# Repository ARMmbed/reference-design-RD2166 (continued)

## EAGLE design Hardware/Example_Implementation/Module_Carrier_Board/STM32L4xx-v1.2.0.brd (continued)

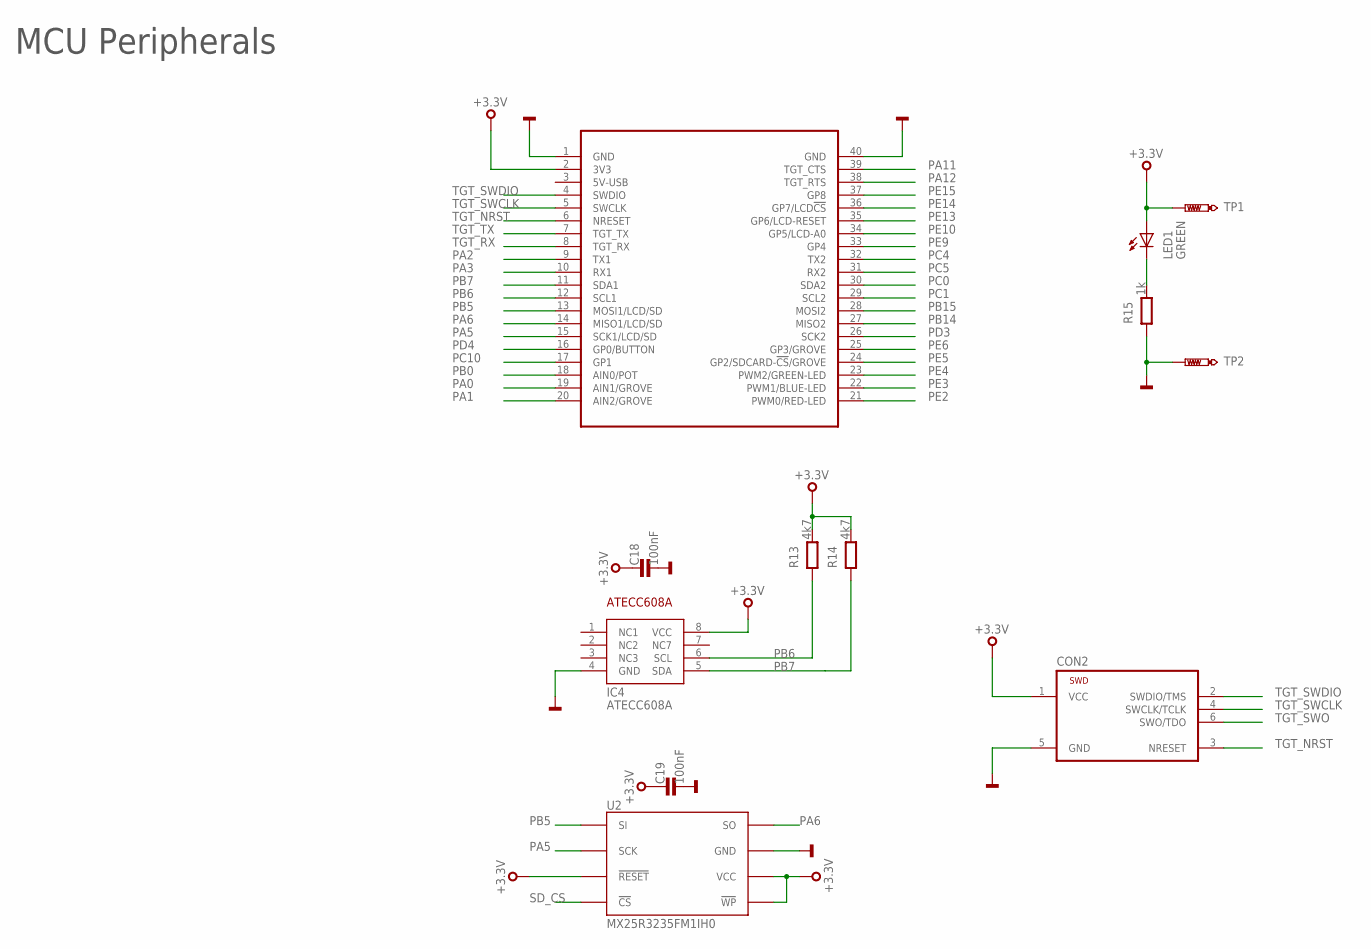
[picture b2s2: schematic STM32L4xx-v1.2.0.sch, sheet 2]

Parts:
C18, C19: 100nF; 0402
CON2: TC2030-CTX-NL
IC4: ATECC608A; SO8
LED1: GREEN; CHIPLED_0603
MOD1: MODULE_DAUGHTER
R13, R14: 4k7; 0402
R15: 1k; 0603
TP1, TP2: TEST_POINT-50R-PTH; TP50-PTH
U2: MX25R3235FM1IH0; SO8

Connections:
+3.3V: C18.1, C19.1, CON2.1 (VCC), IC4.8 (VCC), LED1.A, MOD1.2 (3V3), R13.2, R14.2, TP1.TP, U2.3 (!WP), U2.7 (!RESET), U2.8 (VCC); also elsewhere on the board
GND: C18.2, C19.2, CON2.5 (GND), IC4.4 (GND), MOD1.1 (GND), MOD1.40 (GND), R15.1, TP2.TP, U2.4 (GND); also elsewhere on the board
PA0: MOD1.19 (AIN1/GROVE); also elsewhere on the board
PA1: MOD1.20 (AIN2/GROVE); also elsewhere on the board
PA2: MOD1.9 (TX1); also elsewhere on the board
PA3: MOD1.10 (RX1); also elsewhere on the board
PA5: MOD1.15 (SCK1/LCD/SD), U2.6 (SCK); also elsewhere on the board
PA6: MOD1.14 (MISO1/LCD/SD), U2.2 (SO); also elsewhere on the board
PA11: MOD1.39 (TGT_CTS); also elsewhere on the board
PA12: MOD1.38 (TGT_RTS); also elsewhere on the board
PA_1: LED1.C, R15.2
PB0: MOD1.18 (AIN0/POT); also elsewhere on the board
PB5: MOD1.13 (MOSI1/LCD/SD), U2.5 (SI); also elsewhere on the board
PB6: IC4.6 (SCL), MOD1.12 (SCL1), R13.1; also elsewhere on the board
PB7: IC4.5 (SDA), MOD1.11 (SDA1), R14.1; also elsewhere on the board
PB14: MOD1.27 (MISO2); also elsewhere on the board
PB15: MOD1.28 (MOSI2); also elsewhere on the board
PC0: MOD1.30 (SDA2); also elsewhere on the board
PC1: MOD1.29 (SCL2); also elsewhere on the board
PC4: MOD1.32 (TX2); also elsewhere on the board
PC5: MOD1.31 (RX2); also elsewhere on the board
PC10: MOD1.17 (GP1); also elsewhere on the board
PD3: MOD1.26 (SCK2); also elsewhere on the board
PD4: MOD1.16 (GP0/BUTTON); also elsewhere on the board
PE2: MOD1.21 (PWM0/RED-LED); also elsewhere on the board
PE3: MOD1.22 (PWM1/BLUE-LED); also elsewhere on the board
PE4: MOD1.23 (PWM2/GREEN-LED); also elsewhere on the board
PE5: MOD1.24 (GP2/SDCARD-!CS!/GROVE); also elsewhere on the board
PE6: MOD1.25 (GP3/GROVE); also elsewhere on the board
PE9: MOD1.33 (GP4); also elsewhere on the board
PE10: MOD1.34 (GP5/LCD-A0); also elsewhere on the board
PE13: MOD1.35 (GP6/LCD-RESET); also elsewhere on the board
PE14: MOD1.36 (GP7/LCD!CS); also elsewhere on the board
PE15: MOD1.37 (GP8); also elsewhere on the board
SD_CS: U2.1 (!CS); also elsewhere on the board
TGT_NRST: CON2.3 (NRESET), MOD1.6 (NRESET); also elsewhere on the board
TGT_RX: MOD1.8 (TGT_RX); also elsewhere on the board
TGT_SWCLK: CON2.4 (SWCLK/TCLK), MOD1.5 (SWCLK); also elsewhere on the board
TGT_SWDIO: CON2.2 (SWDIO/TMS), MOD1.4 (SWDIO); also elsewhere on the board
TGT_SWO: CON2.6 (SWO/TDO); also elsewhere on the board
TGT_TX: MOD1.7 (TGT_TX); also elsewhere on the board

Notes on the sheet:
MCU Peripherals

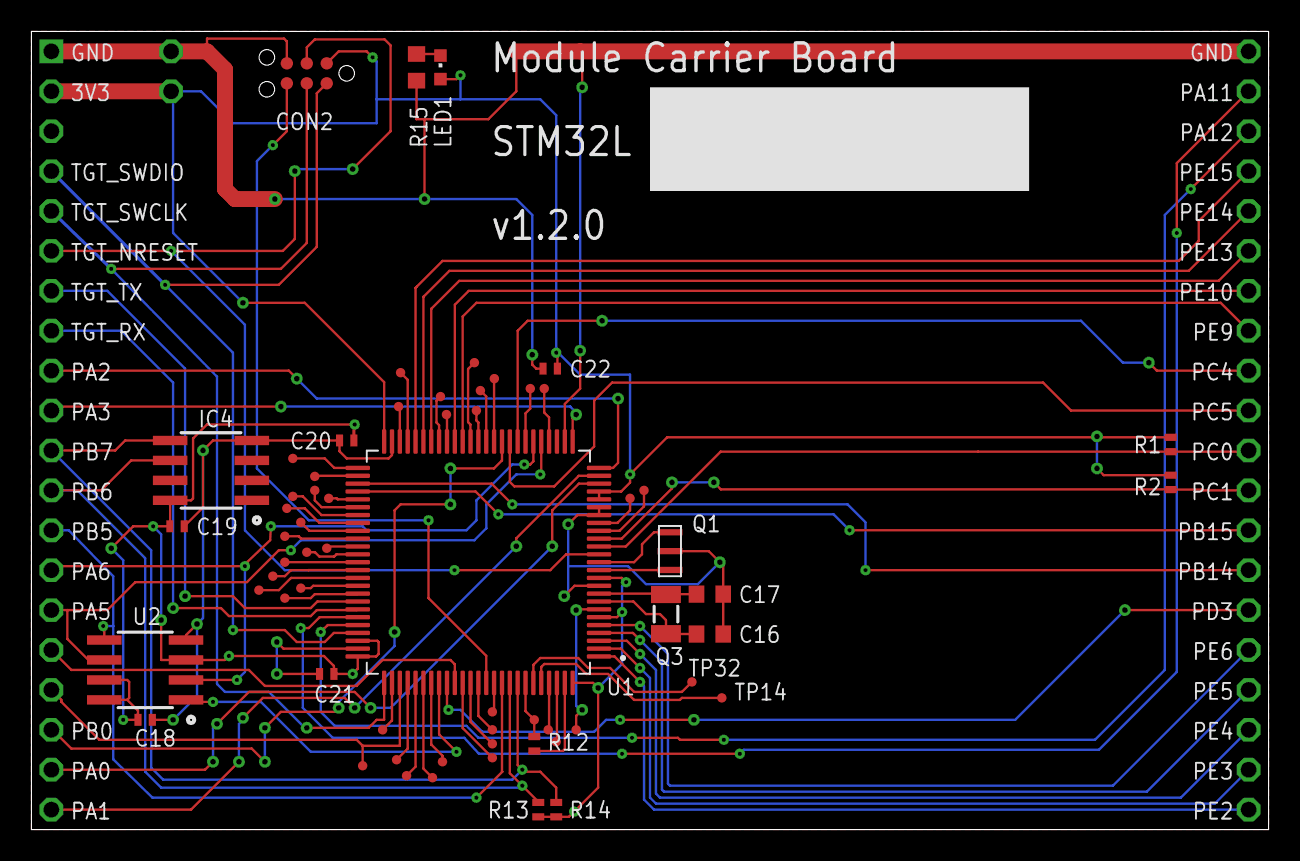
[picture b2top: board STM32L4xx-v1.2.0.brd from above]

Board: 2 copper layers, 78.7 x 50.8 mm, 66 parts (0 on the bottom side), 87 nets.

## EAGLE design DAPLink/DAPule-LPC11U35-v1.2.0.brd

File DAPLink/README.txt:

/*********************************
        DAPule
*********************************/

There are many flavours of DAPule available with different MCU's such as an LPC11U35, K20D, KL26Z and others.

For the purposes of this reference design, we have used an LPC11U35 based DAPule, schematics and design files 
for which have been shared in this directory.

Also, a binary file that was used for development of this RD2166 on the MTB (schematics and design files also
shared) is available for use.

For any issues, please use the RD2166's GitHub repo to report issues.

       ********** End of document *********

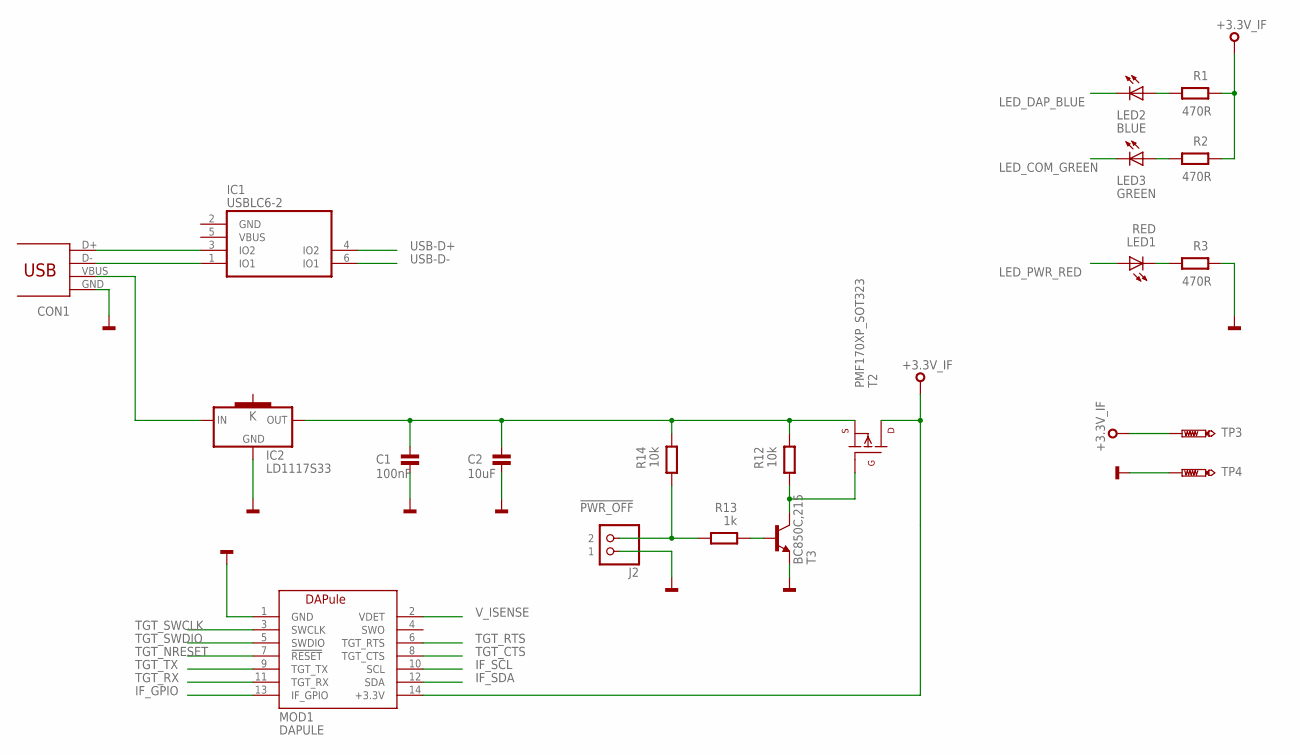
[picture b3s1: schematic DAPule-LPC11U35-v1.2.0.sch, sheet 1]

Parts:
C1: 100nF; 0603
C2: 10uF; 0603
CON1: USB_MICROB; MOLEX-47364-0001
IC1: USBLC6-2SC6; SOT23-6L
IC2: LD1117S33; SOT223
J2: PINHD-1X2; 1X02
LED1: RED; CHIPLED_0603
LED2: BLUE; CHIPLED_0603
LED3: GREEN; CHIPLED_0603
MOD1: DAPULE
R1, R2, R3: 470R; 0603@1
R12, R14: 10k; 0603@1
R13: 1k; 0603@1
T2: PMF170XP_SOT323; SOT323-BEC
T3: BC850C,215; SOT23-3
TP3, TP4: TEST-POINT-50R-PTH; TP50-PTH

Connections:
!PWR_OFF: J2.2, R13.2, R14.2
+3.3V_IF: MOD1.14 (+3.3V), R1.1, R2.1, T2.C (D), TP3.TP; also elsewhere on the board
GND: C1.2, C2.2, CON1.GND, IC2.1 (GND), J2.1, MOD1.1 (GND), R3.1, T3.2 (E), TP4.TP; also elsewhere on the board
IF_GPIO: MOD1.13 (IF_GPIO); also elsewhere on the board
IF_SCL: MOD1.10 (SCL); also elsewhere on the board
IF_SDA: MOD1.12 (SDA); also elsewhere on the board
LED_COM_GREEN: LED3.C; also elsewhere on the board
LED_DAP_BLUE: LED2.C; also elsewhere on the board
LED_PWR_RED: LED1.A; also elsewhere on the board
unnamed: LED3.A, R2.2
unnamed: CON1.D-, IC1.1 (IO1)
unnamed: CON1.D+, IC1.3 (IO2)
unnamed: LED2.A, R1.2
unnamed: C1.1, C2.1, IC2.2 (OUT), R12.1, R14.1, T2.E (S)
unnamed: LED1.C, R3.2
unnamed: CON1.VBUS, IC2.3 (IN)
unnamed: R13.1, T3.1 (B)
unnamed: R12.2, T2.B (G), T3.3 (C)
TGT_CTS: MOD1.8 (TGT_CTS); also elsewhere on the board
TGT_NRESET: MOD1.7 (!RESET); also elsewhere on the board
TGT_RTS: MOD1.6 (TGT_RTS); also elsewhere on the board
TGT_RX: MOD1.11 (TGT_RX); also elsewhere on the board
TGT_SWCLK: MOD1.3 (SWCLK); also elsewhere on the board
TGT_SWDIO: MOD1.5 (SWDIO); also elsewhere on the board
TGT_TX: MOD1.9 (TGT_TX); also elsewhere on the board
USB-D+: IC1.4 (IO2); also elsewhere on the board
USB-D-: IC1.6 (IO1); also elsewhere on the board
V_ISENSE: MOD1.2 (VDET); also elsewhere on the board

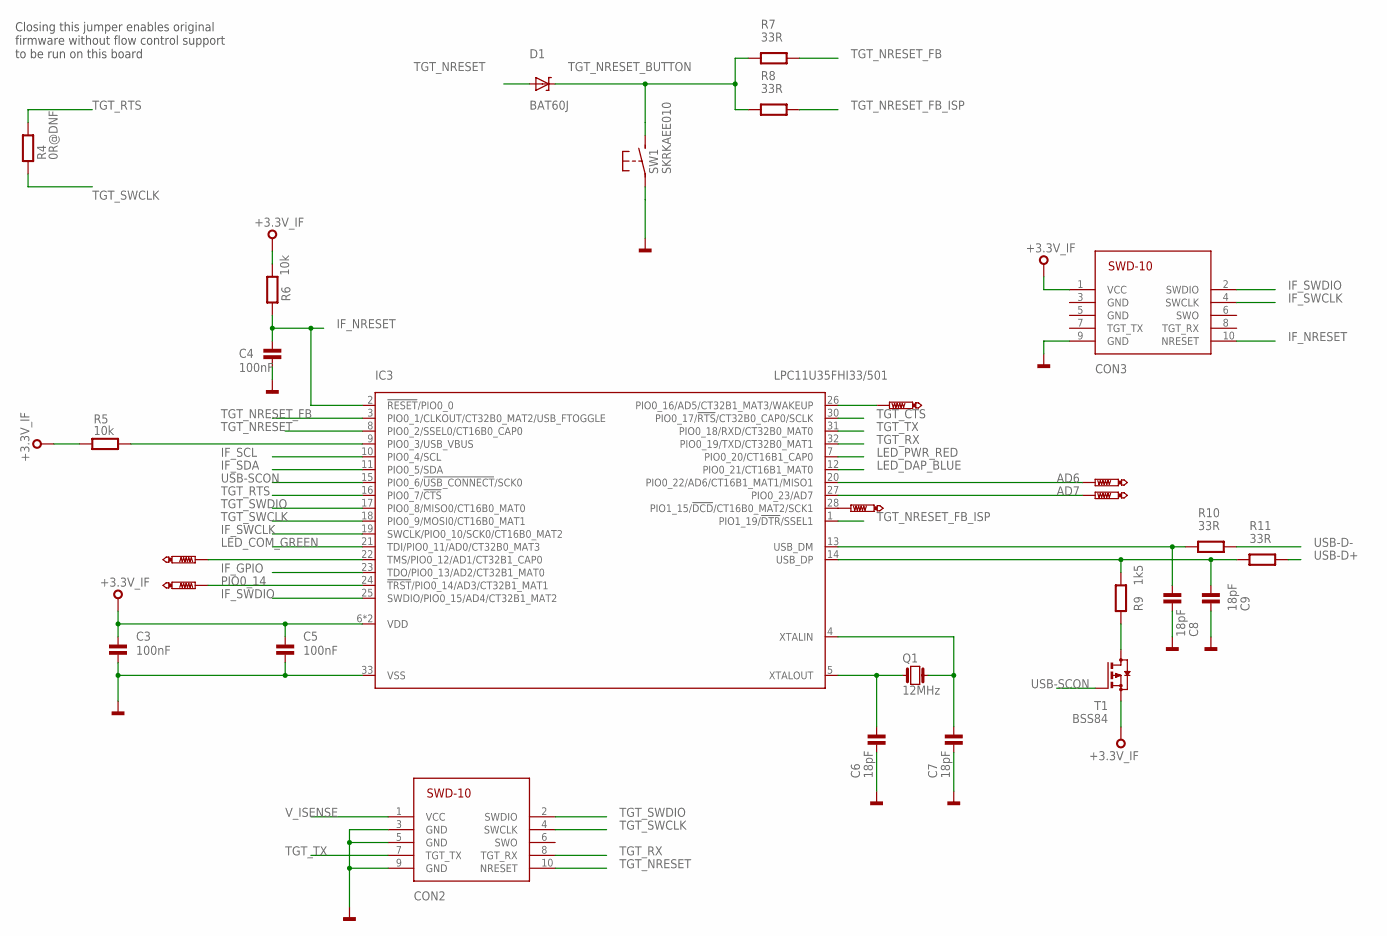
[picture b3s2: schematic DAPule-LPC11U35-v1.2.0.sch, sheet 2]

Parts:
C3, C4, C5: 100nF; 0603
C6, C7, C8, C9: 18pF; 0603
CON2, CON3: SWD-10/TC2050_SMD; FTSH-105-02
D1: BAT60J; SOD323
IC3: LPC11U35FHI33/501; SOT617-3
Q1: 12MHz; 3.2X.2.5
R4: 0R@DNF; 0402@1
R5, R6: 10k; 0603@1
R7, R8, R10, R11: 33R; 0603@1
R9: 1k5; 0603@1
SW1: SKRKAEE010
T1: BSS84; SOT23
TP1, TP2, TP5, TP8, TP9, TP13: PTR1TP07R; TP07R

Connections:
+3.3V_IF: C3.1, C5.1, CON3.1 (VCC), IC3.6 (VDD), IC3.29 (VDD), R5.2, R6.2, T1.2 (S); also elsewhere on the board
AD6: IC3.20 (PIO0_22/AD6/CT16B1_MAT1/MISO1), TP9.TP
AD7: IC3.27 (PIO0_23/AD7), TP8.TP
GND: C3.2, C4.2, C5.2, C6.2, C7.2, C8.2, C9.2, CON2.3 (GND), CON2.5 (GND), CON2.9 (GND), CON3.9 (GND), IC3.33 (VSS), SW1.P$1; also elsewhere on the board
IF_GPIO: IC3.23 (TDO/PIO0_13/AD2/CT32B1_MAT0); also elsewhere on the board
IF_NRESET: C4.1, CON3.10 (NRESET), IC3.2 (!RESET!/PIO0_0), R6.1
IF_SCL: IC3.10 (PIO0_4/SCL); also elsewhere on the board
IF_SDA: IC3.11 (PIO0_5/SDA); also elsewhere on the board
IF_SWCLK: CON3.4 (SWCLK), IC3.19 (SWCLK/PIO0_10/SCK0/CT16B0_MAT2)
IF_SWDIO: CON3.2 (SWDIO), IC3.25 (SWDIO/PIO0_15/AD4/CT32B1_MAT2)
LED_COM_GREEN: IC3.21 (TDI/PIO0_11/AD0/CT32B0_MAT3); also elsewhere on the board
LED_DAP_BLUE: IC3.12 (PIO0_21/CT16B1_MAT0); also elsewhere on the board
LED_PWR_RED: IC3.7 (PIO0_20/CT16B1_CAP0); also elsewhere on the board
unnamed: IC3.22 (TMS/PIO0_12/AD1/CT32B1_CAP0), TP1.TP
unnamed: IC3.26 (PIO0_16/AD5/CT32B1_MAT3/WAKEUP), TP2.TP
unnamed: IC3.28 (PIO1_15/!DCD!/CT16B0_MAT2/SCK1), TP5.TP
unnamed: C6.1, IC3.5 (XTALOUT), Q1.P$1 (1)
unnamed: C7.1, IC3.4 (XTALIN), Q1.P$3 (2)
unnamed: IC3.9 (PIO0_3/USB_VBUS), R5.1
unnamed: R9.1, T1.3 (D)
PIO0_14: IC3.24 (!TRST!/PIO0_14/AD3/CT32B1_MAT1), TP13.TP
TGT_CTS: IC3.30 (PIO0_17/!RTS!/CT32B0_CAP0/SCLK); also elsewhere on the board
TGT_NRESET: CON2.10 (NRESET), D1.A, IC3.8 (PIO0_2/SSEL0/CT16B0_CAP0); also elsewhere on the board
TGT_NRESET_BUTTON: D1.K, R7.2, R8.2, SW1.P$2 (S)
TGT_NRESET_FB: IC3.3 (PIO0_1/CLKOUT/CT32B0_MAT2/USB_FTOGGLE), R7.1
TGT_NRESET_FB_ISP: IC3.1 (PIO1_19/!DTR!/SSEL1), R8.1
TGT_RTS: IC3.16 (PIO0_7/!CTS!), R4.2; also elsewhere on the board
TGT_RX: CON2.8 (TGT_RX), IC3.32 (PIO0_19/TXD/CT32B0_MAT1); also elsewhere on the board
TGT_SWCLK: CON2.4 (SWCLK), IC3.18 (PIO0_9/MOSI0/CT16B0_MAT1), R4.1; also elsewhere on the board
TGT_SWDIO: CON2.2 (SWDIO), IC3.17 (PIO0_8/MISO0/CT16B0_MAT0); also elsewhere on the board
TGT_TX: CON2.7 (TGT_TX), IC3.31 (PIO0_18/RXD/CT32B0_MAT0); also elsewhere on the board
USB-D+: R11.1; also elsewhere on the board
USB-D-: R10.1; also elsewhere on the board
USB-SCON: IC3.15 (PIO0_6/!USB_CONNECT!/SCK0), T1.1 (G)
USB_DM: C8.1, IC3.13 (USB_DM), R10.2
USB_DP: C9.1, IC3.14 (USB_DP), R9.2, R11.2
V_ISENSE: CON2.1 (VCC); also elsewhere on the board

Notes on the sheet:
Closing this jumper enables original firmware without flow control support to be run on this board

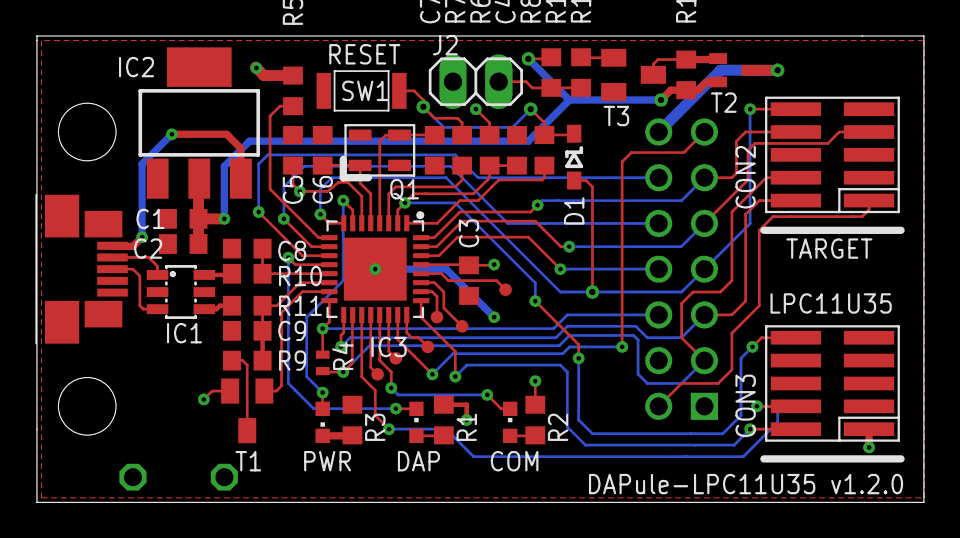
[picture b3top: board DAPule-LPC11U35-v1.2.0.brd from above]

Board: 2 copper layers, 49.3 x 25.9 mm, 48 parts (0 on the bottom side), 47 nets.

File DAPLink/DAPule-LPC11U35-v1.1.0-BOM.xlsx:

Qty | Value | Device | Package | Parts | Description | MF | MFN | OC-DIGIKEY | OC-MOUSER | OC-NEWARK | SRAM | TP_SIGNAL_NAME | Column1
1 | 0R@DNF | R0402 | 0402@1 | R4
4 | 100nF | C0603 | 0603 | C1, C3, C4, C5 | Capacitor
2 | 10k | R0603 | 0603@1 | R5, R6
1 | 10uF | C0603 | 0603 | C2 | Capacitor
1 | 12MHz | Q_3.2X2.5 | 3.2X.2.5 | Q1
4 | 18pF | C0603 | 0603 | C6, C7, C8, C9 | Capacitor
1 | 1k5 | R0603 | 0603@1 | R9
4 | 33R | R0603 | 0603@1 | R7, R8, R10, R11
3 | 470R | R0603 | 0603@1 | R1, R2, R3
1 | BAT60J | BAT60J | SOD323 | D1 | SCHOTTKY DIODE | STMicroelectronics | BAT60JFILM | 497-3707-6-ND | 511-BAT60JFILM | 89K1218
1 | BLUE | LED0603 | CHIPLED_0603 | LED2 | SMD LED
1 | BSS84 | BSS84 | SOT23 | T1 | P-CHANNEL MOS FET
1 | No Fit | No Fit | No Fit | MOD1 | No Fit
1 | GREEN | LED0603 | CHIPLED_0603 | LED3 | SMD LED
1 | LD1117S33 | LD1117S33 | SOT223 | IC2 | VOLTAGE REGULATOR SMD 3,3V
1 | LPC11U35FHI33/501 | LPC11U35FHI33/501 | SOT617-3 | IC3 | 32-bit ARM Cortex-M0 microcontroller; up to 128 kB flash; up |  |  |  |  |  | 12kB
6 | PTR1TP07R | PTR1TP07R | TP07R | TP1, TP2, TP5, TP8, TP9, TP13 | TEST PIN
1 | RED | LED0603 | CHIPLED_0603 | LED1 | SMD LED
1 | SKRKAEE010 | SKRKAEE010 | SKRKAEE010 | SW1 | MOMENTARY SWITCH PUSH VERTICAL (SPST) | ALPS | SKRKAEE010 |  | 688-SKRKAE
2 | SWD-10/TC2050_SMD | SWD-10/TC2050_SMD | FTSH-105-02 | CON2, CON3 | 1mm pitch 10-Pin Cortex Programming Header with optional TC2050 footprint solde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
2 | TEST-POINT-50R-PTH | TEST-POINT-50R-PTH | TP50-PTH | TP3, TP4
1 | USBLC6-2SC6 | USBLC6-2SC6 | SOT23-6L | IC1
1 | USB_MICROB | USB_MICROB | MOLEX-47364-0001 | CON1 | USB Connectors

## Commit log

2019-02-26 First commit Adding everything
2019-02-26 Docs improvements
2019-02-26 Formatting
2019-02-26 Cosmetic changes
2019-02-26 Docs improvement for SIM creds
2019-02-27 Adding Hardware design files
2019-02-27 Removing redundant BOM files
2019-02-27 Documentation improvements And also removed my mbed credentials.
2019-02-28 Adding DAPule hardware related files
2019-02-28 Adding v1.2.0 hardware files for DAPule
2019-02-28 Adding ERRATA for MCB
2019-03-01 Adding v1.2.0 (& remove v1.1.0) files for MCB & MEB
2019-04-24 Update mbed_app.json
    Changing description format of NVSTORE regions & reducing to 2K instead of 4K.
2019-04-24 Update mbed_app.json
    Removing redundant code.
